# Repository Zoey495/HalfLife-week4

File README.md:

# HalfLife-week4
The process of following a guide made by HalfLife

In this project, I will be making a timer/countdown, which can be increased or decreased based on the inputs given by the switches.

---------------------

Using Kicad, I first made a schematic diagram, planning what components to use and how they would be connected to one another.

Using Kicad's PCB editor mode, I designed the board where all the parts would sit and how they would be wired/connected to one another.

Then using the arduino ide software program, I wrote the code that told the Raspberry Pico Pi what to do and where all the components were connected.

All the files can be found in the folder "Hardware_Software".

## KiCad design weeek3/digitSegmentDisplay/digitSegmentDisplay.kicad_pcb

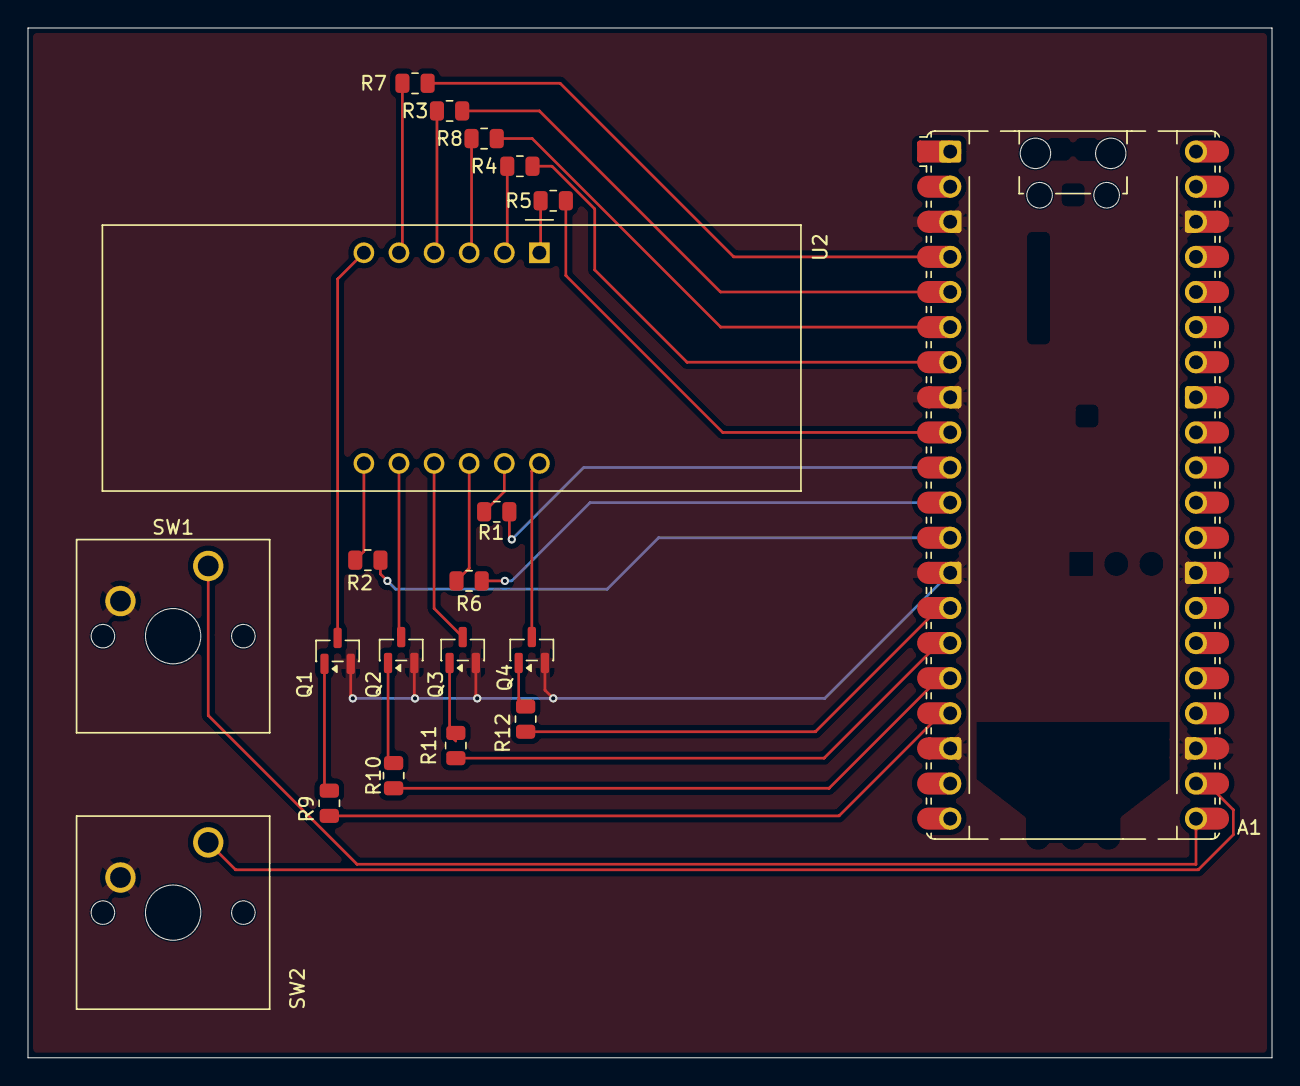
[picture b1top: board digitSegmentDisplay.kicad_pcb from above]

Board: 2 copper layers, 90.0 x 74.5 mm, 20 parts (0 on the bottom side), 31 nets.

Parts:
A1: RaspberryPi_Pico; RaspberryPi_Pico_Common_Unspecified
Q1, Q2, Q3, Q4: BC817; SOT-23
R1, R2, R3, R4, R5, R6, R7, R8: R_220; R_0805_2012Metric
R9, R10, R11, R12: R_1000; R_0805_2012Metric
SW1, SW2: SW_Push; SW_Cherry_MX_1.00u_PCB
U2: CC56-12EWA; CA56-12EWA

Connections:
/D1: Q1.3 (C), U2.6 (CC4)
/D2: Q2.3 (C), U2.8 (CC3)
/D3: Q3.3 (C), U2.9 (CC2)
/D4: Q4.3 (C), U2.12 (CC1)
/DP1: A1.17 (GPIO13), R9.1
/DP2: A1.16 (GPIO12), R10.1
/DP3: A1.15 (GPIO11), R11.1
/DP4: A1.14 (GPIO10), R12.1
/DPX: A1.12 (GPIO9), R2.1
/GND: A1.3 (GND), A1.8 (GND), A1.13 (GND), A1.18 (GND), A1.23 (GND), A1.28 (GND), A1.38 (GND), Q1.2 (E), Q2.2 (E), Q3.2 (E), Q4.2 (E), SW1.2, SW2.2
/SW_1: A1.21 (GPIO16), SW1.1
/SW_2: A1.22 (GPIO17), SW2.1
/a: A1.4 (GPIO2), R7.1
/b: A1.5 (GPIO3), R3.1
/c: A1.6 (GPIO4), R8.1
/d: A1.7 (GPIO5), R4.1
/e: A1.9 (GPIO6), R5.1
/f: A1.10 (GPIO7), R1.1
/g: A1.11 (GPIO8), R6.1
unnamed: Q1.1 (B), R9.2
unnamed: Q2.1 (B), R10.2
unnamed: Q3.1 (B), R11.2
unnamed: Q4.1 (B), R12.2
unnamed: R8.2, U2.3 (DPX)
unnamed: R1.2, U2.11 (a)
unnamed: R2.2, U2.7 (b)
unnamed: R3.2, U2.4 (c)
unnamed: R4.2, U2.2 (d)
unnamed: R5.2, U2.1 (e)
unnamed: R6.2, U2.10 (f)
unnamed: R7.2, U2.5 (g)
